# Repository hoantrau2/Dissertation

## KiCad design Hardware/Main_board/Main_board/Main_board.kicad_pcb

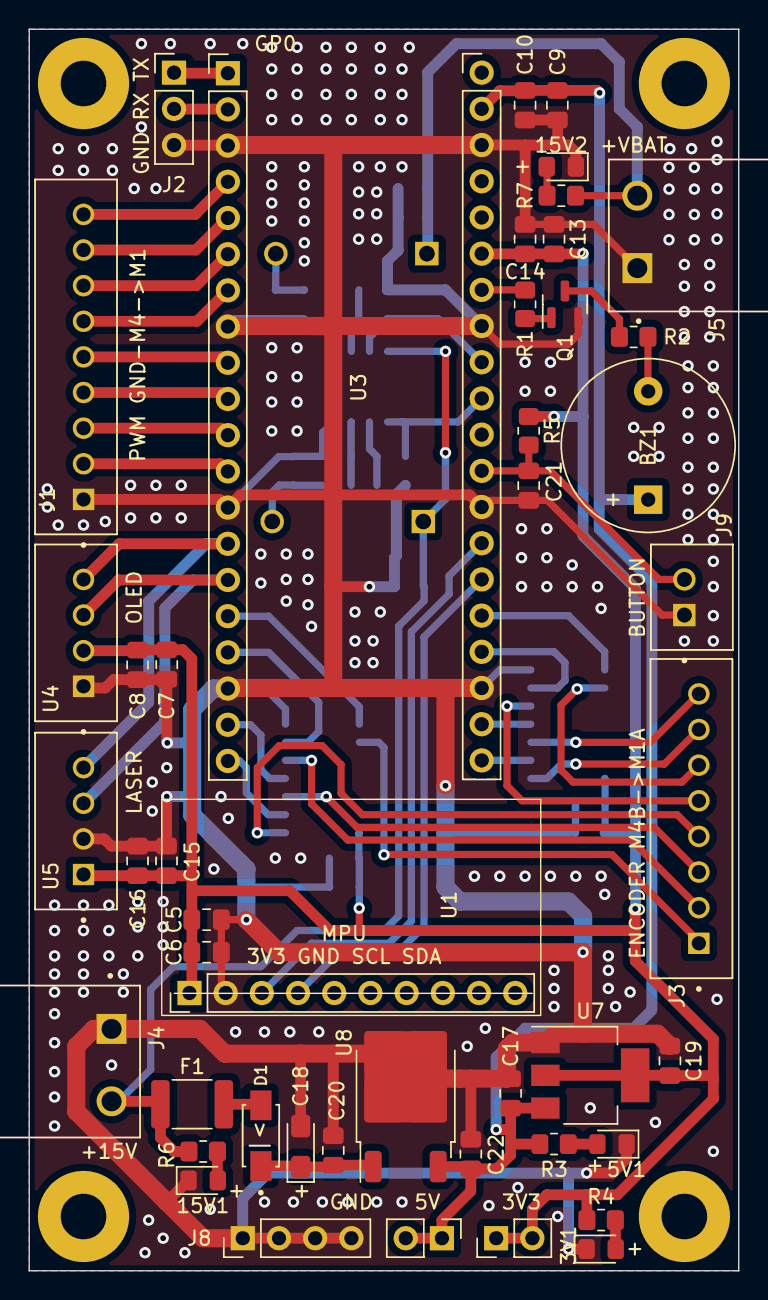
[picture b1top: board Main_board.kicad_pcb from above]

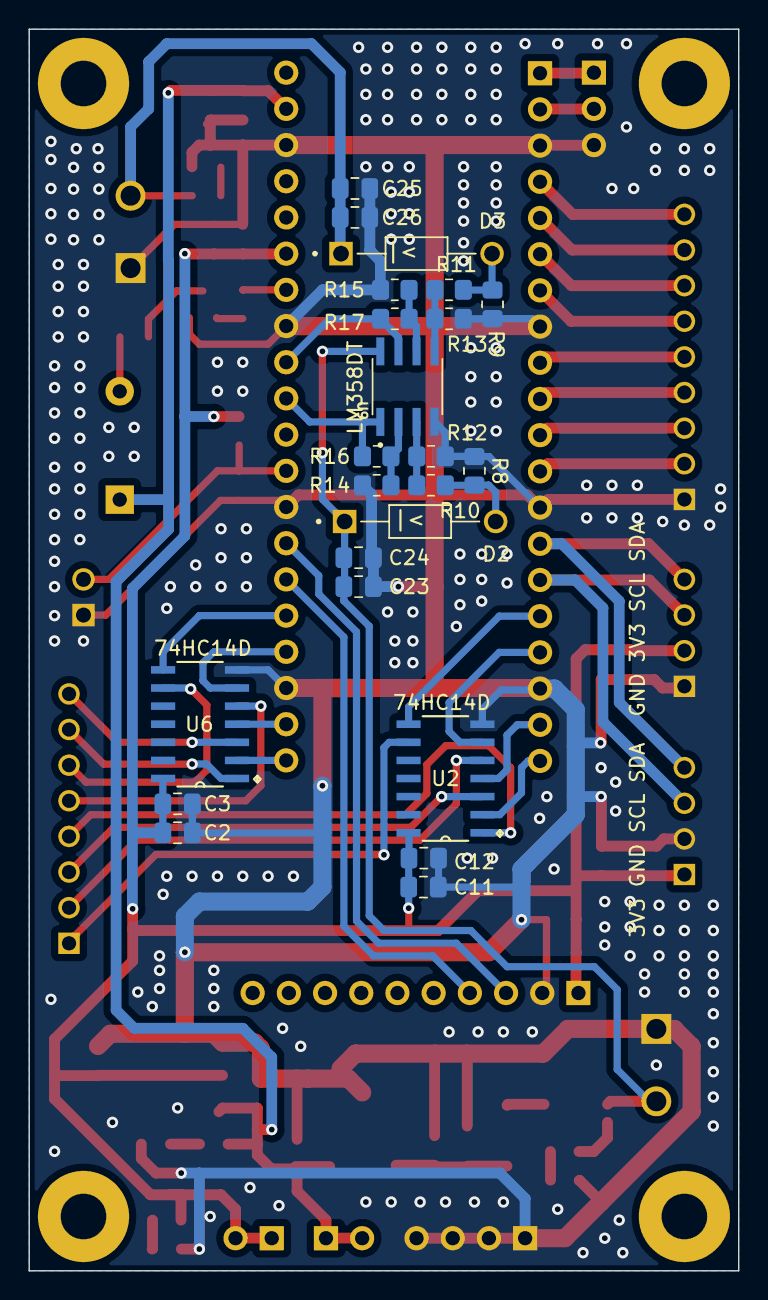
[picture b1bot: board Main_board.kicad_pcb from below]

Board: 2 copper layers, 49.8 x 87.1 mm, 73 parts (23 on the bottom side), 54 nets.

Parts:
3V1, 5V1, 15V1, 15V2: LED; LED_0805_2012Metric_Pad1.15x1.40mm_HandSolder
BZ1: Buzzer; Buzzer_12x9.5RM7.6
C2, C5, C7, C9, C11, C13, C15, C23, C25: 1u; C_0805_2012Metric_Pad1.18x1.45mm_HandSolder
C3, C6, C8, C10, C12, C14, C16, C17, C19, C21, C24, C26: 100n; C_0805_2012Metric_Pad1.18x1.45mm_HandSolder
C18: 1u, 16V; CP_EIA-3216-18_Kemet-A_Pad1.58x1.35mm_HandSolder
C20, C22: 100nF,50V; C_0805_2012Metric_Pad1.18x1.45mm_HandSolder
D1: RS1M; DIOM4330X250N
D2, D3: 1N4742A; DIOAD1060W70L435D230
F1: Fuse; Fuse_1812_4532Metric_Pad1.30x3.40mm_HandSolder
H1, H2, H3, H4: MountingHole; MountingHole_3.2mm_M3_Pad
J1: B9B-XH-A(LF)(SN); JST_B9B-XH-A(LF)(SN)
J2: Conn_01x03_Pin; PinHeader_1x03_P2.54mm_Vertical
J3: B8B-XH-A(LF)(SN); JST_B8B-XH-A(LF)(SN)
J4, J5: 282814-2; TE_282814-2
J6: Power 5V; PinHeader_1x02_P2.54mm_Vertical
J7: Power 3v3; PinHeader_1x02_P2.54mm_Vertical
J8: GND; PinHeader_1x04_P2.54mm_Vertical
J9: Button 1; JST_B2B-XH-A(LF)(SN)
Q1: 2SC1815; SOT-23
R1: 1k2; R_0805_2012Metric_Pad1.20x1.40mm_HandSolder
R2: 0R; R_0805_2012Metric_Pad1.20x1.40mm_HandSolder
R3: 1k; R_0805_2012Metric_Pad1.20x1.40mm_HandSolder
R4: 330; R_0805_2012Metric_Pad1.20x1.40mm_HandSolder
R5, R6, R7, R12, R13, R16, R17: 10k; R_0805_2012Metric_Pad1.20x1.40mm_HandSolder
R8, R9: 100k; R_0805_2012Metric_Pad1.20x1.40mm_HandSolder
R10, R11, R14, R15: 20k; R_0805_2012Metric_Pad1.20x1.40mm_HandSolder
U1: MPU9250
U2, U6: 74HC14D; SOIC127P600X175-14N
U3: pico_pin
U4, U5: JST_B4B-XH-A(LF)(SN)
U7: AMS1117-3.3; SOT-223-3_TabPin2
U8: L7805; TO-252-2
U9: LM358DT; SOIC127P600X175-8N

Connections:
+3V3: C2.2, C3.2, C5.2, C6.2, C7.2, C8.2, C11.2, C12.2, C13.2, C14.2, C15.2, C16.2, C19.2, J7.1, J7.2, R4.1, R5.1, U1.1 (VCC), U2.14 (VCC), U3.35, U4.2 (VCC), U5.1 (VIN), U6.14 (VCC), U7.2 (VO)
+5V: BZ1.1 (-), C9.2, C10.2, C17.2, C22.2, J6.1, J6.2, R3.1, U3.39, U7.3 (VI), U8.3 (OUT)
+15V: C23.1, C24.2, D2.C, F1.1, J4.2, R6.1, U9.8 (VCC+)
/RX: J2.2, U3.2
/TX: J2.1, U3.1
ADC0: R16.1, U3.31, U9.1 (OUT1)
ADC1: R17.1, U3.32, U9.7 (OUT2)
BUZZER1: R1.2, U3.34
Button1: C21.2, J9.2, R5.2, U3.29
GND: 3V1.1 (K), 5V1.1 (K), 15V1.1 (K), 15V2.1 (K), C2.1, C3.1, C5.1, C6.1, C7.1, C8.1, C9.1, C10.1, C11.1, C12.1, C13.1, C14.1, C15.1, C16.1, C17.1, C18.2, C19.1, C20.1, C21.1, C22.1, C23.2, C24.1, C25.2, C26.1, J1.1, J2.3, J4.1, J5.1, J8.1, J8.2, J8.3, J8.4, J9.1, Q1.2 (E), R8.2, R9.2, R12.2, R13.2, R14.1, R15.1, U1.2 (GND), U2.7 (GND), U3.3, U3.8, U3.13, U3.18, U3.23, U3.28, U3.33, U3.38, U4.1 (GND), U5.2 (GND), U6.7 (GND), U7.1 (GND), U8.2 (GND), U9.4 (VCC-)
M1_ENC_A: J3.8, U6.3 (2A)
M1_ENC_A': U3.22, U6.4 (2Y)
M1_ENC_B: J3.7, U6.1 (1A)
M1_ENC_B': U3.21, U6.2 (1Y)
M1_PWM_L: J1.8, U3.5
M1_PWM_R: J1.9, U3.4
M2_ENC_A: J3.6, U6.9 (4A)
M2_ENC_A': U3.25, U6.8 (4Y)
M2_ENC_B: J3.5, U6.5 (3A)
M2_ENC_B': U3.24, U6.6 (3Y)
M2_PWM_L: J1.6, U3.7
M2_PWM_R: J1.7, U3.6
M3_ENC_A: J3.4, U2.1 (1A)
M3_ENC_A': U2.2 (1Y), U3.20
M3_ENC_B: J3.3, U2.3 (2A)
M3_ENC_B': U2.4 (2Y), U3.19
M3_PWM_L: J1.4, U3.10
M3_PWM_R: J1.5, U3.9
M4_ENC_A: J3.2, U2.5 (3A)
M4_ENC_A': U2.6 (3Y), U3.17
M4_ENC_B: J3.1, U2.9 (4A)
M4_ENC_B': U2.8 (4Y), U3.16
M4_PWM_L: J1.2, U3.12
M4_PWM_R: J1.3, U3.11
MPU_SCL: U1.3 (SCL), U3.27
MPU_SDA: U1.4 (SDA), U3.26
unnamed: 3V1.2 (A), R4.2
unnamed: 5V1.2 (A), R3.2
unnamed: 15V1.2 (A), R6.2
unnamed: 15V2.2 (A), R7.2
unnamed: BZ1.2 (+), R2.1
unnamed: D1.A, F1.2
unnamed: D2.A, R8.1, R10.1
unnamed: D3.A, R9.1, R11.1
unnamed: Q1.1 (B), R1.1
unnamed: Q1.3 (C), R2.2
unnamed: C18.1, C20.2, D1.C, U8.1 (IN)
unnamed: R10.2, R12.1, U9.3 (IN1+)
unnamed: R14.2, R16.2, U9.2 (IN1-)
unnamed: R11.2, R13.1, U9.5 (IN2+)
unnamed: R15.2, R17.2, U9.6 (IN2-)
OLED_LASER_SCL: U3.15, U4.3 (SCK), U5.3 (SCL)
OLED_LASER_SDA: U3.14, U4.4 (SDA), U5.4 (SDA)
V_bat: C25.1, C26.2, D3.C, J5.2, R7.1

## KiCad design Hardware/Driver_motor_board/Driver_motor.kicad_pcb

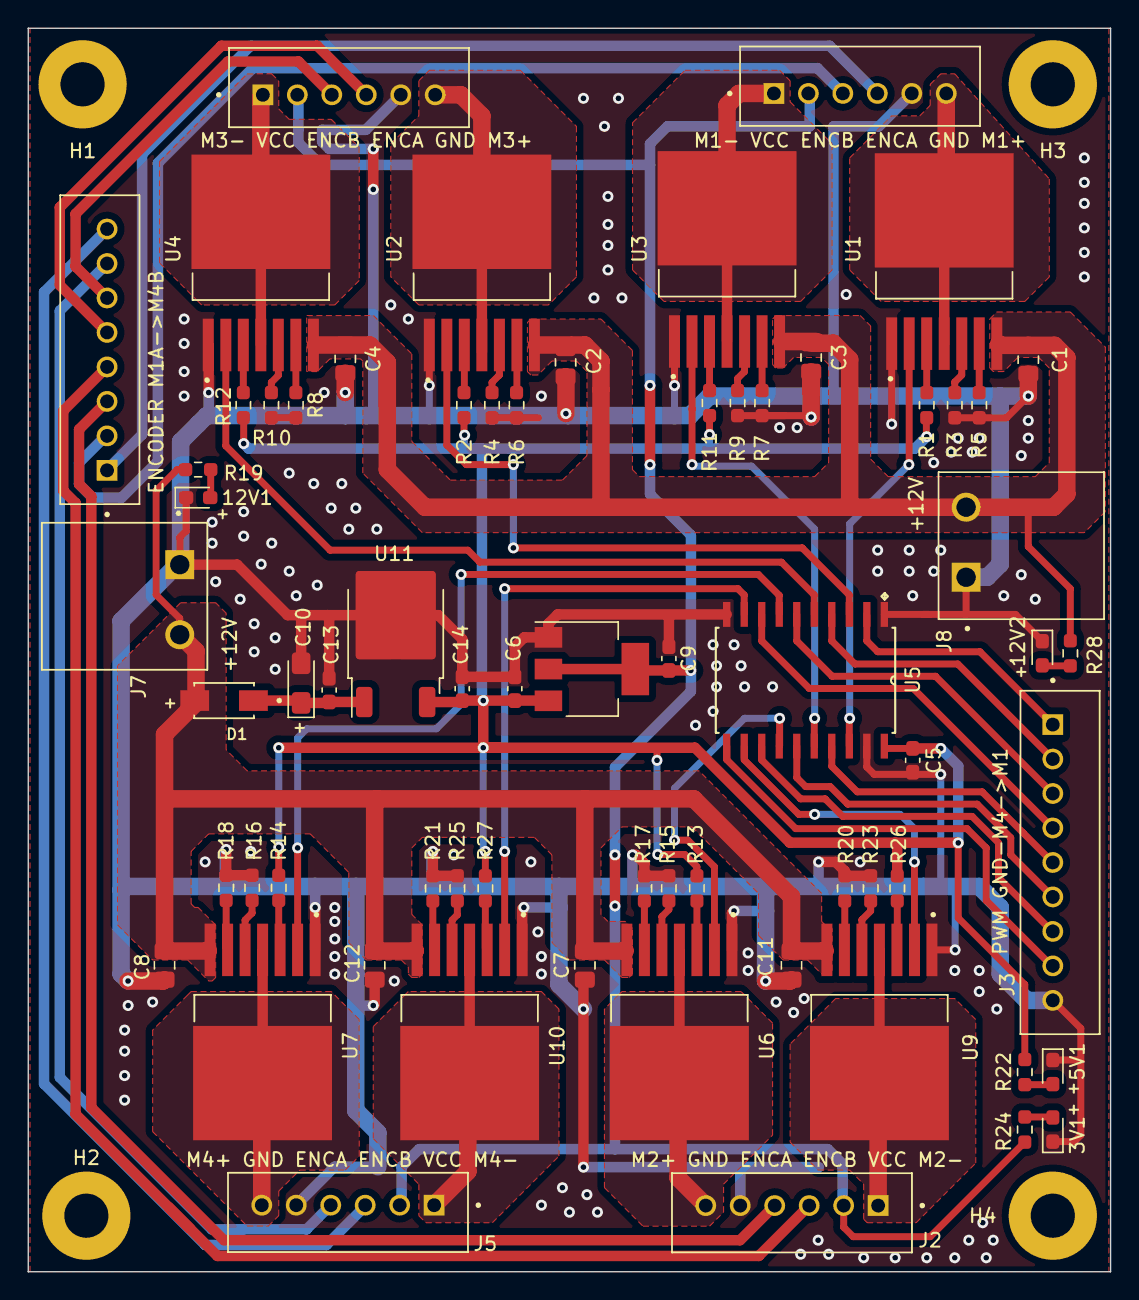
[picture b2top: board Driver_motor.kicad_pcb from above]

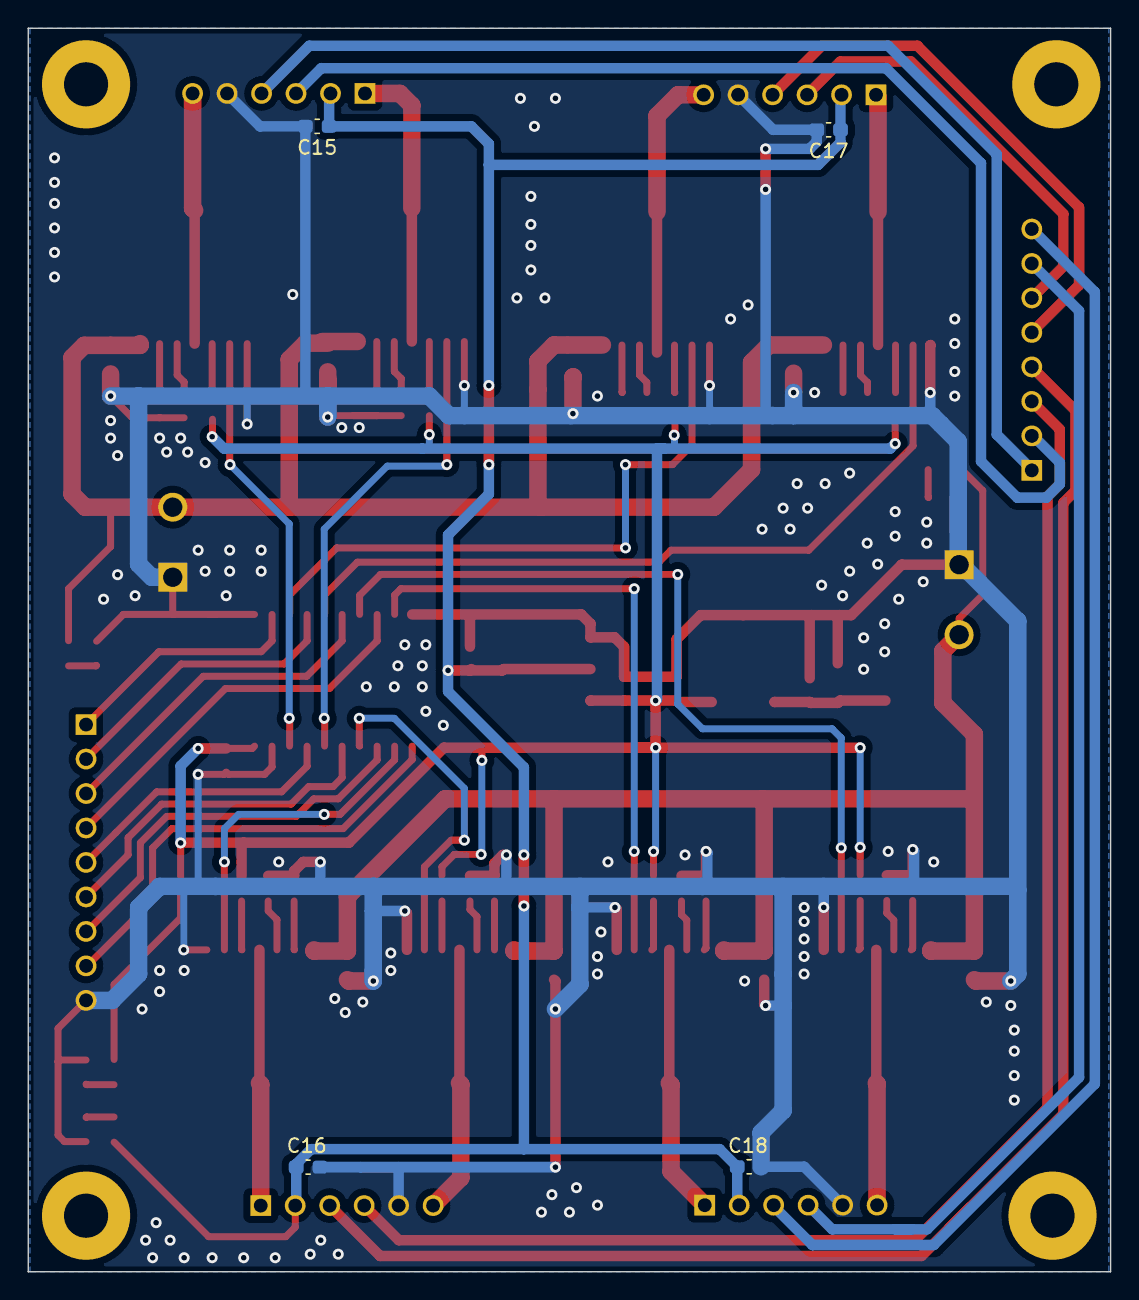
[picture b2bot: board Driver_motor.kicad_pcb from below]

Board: 2 copper layers, 78.5 x 90.2 mm, 74 parts (4 on the bottom side), 66 nets.

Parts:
3V1, 5V1, 12V1, 12V2: LED; LED_0603_1608Metric_Pad1.05x0.95mm_HandSolder
C1, C2, C3, C4, C7, C8, C11, C12: 470nF; C_0805_2012Metric_Pad1.18x1.45mm_HandSolder
C5: 100nF; C_0603_1608Metric_Pad1.08x0.95mm_HandSolder
C6, C9, C15, C16, C17, C18: 100n; C_0603_1608Metric_Pad1.08x0.95mm_HandSolder
C10: 1u, 16V; CP_EIA-3216-18_Kemet-A_Pad1.58x1.35mm_HandSolder
C13, C14: 100nF,50V; C_0603_1608Metric_Pad1.08x0.95mm_HandSolder
D1: RS1M; DIOM4330X250N
H1, H2, H3, H4: MountingHole; MountingHole_3.2mm_M3_Pad
J1, J2, J4, J5: B6B-XH-A(LF)(SN); JST_B6B-XH-A(LF)(SN)
J3: B9B-XH-A(LF)(SN); JST_B9B-XH-A(LF)(SN)
J6: B8B-XH-A(LF)(SN); JST_B8B-XH-A(LF)(SN)
J7, J8: 282814-2; TE_282814-2
R1, R2, R3, R4, R9, R10, R11, R12, R13, R14, R15, R16, R19, R23, R25, R26, R27, R28: 10k; R_0603_1608Metric_Pad0.98x0.95mm_HandSolder
R5, R6, R7, R8, R17, R18, R20, R21, R22: 1k; R_0603_1608Metric_Pad0.98x0.95mm_HandSolder
R24: 330; R_0603_1608Metric_Pad0.98x0.95mm_HandSolder
U1, U2, U3, U4, U6, U7, U9, U10: BTS7960B; DPAK127P1490X440-8N
U5: 74HC244; SOIC127P1032X265-20N
U8: AMS1117-3.3; SOT-223-3_TabPin2
U11: L7805; TO-252-2

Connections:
+3.3V: C9.2, C15.2, C16.2, C17.2, C18.2, J1.2, J2.2, J4.2, J5.2, R24.1, U8.2 (VO)
+5V: C5.1, C6.2, C14.2, R1.1, R2.1, R11.1, R12.1, R13.1, R14.1, R22.1, R26.1, R27.1, U5.20 (VCC), U8.3 (VI), U11.3 (OUT)
+12P: C1.2, C2.2, C3.1, C4.1, J8.2, R28.1, U1.7 (VS), U2.7 (VS), U3.7 (VS), U4.7 (VS)
+12V: C7.2, C8.2, C11.1, C12.1, D1.A, J7.2, R19.1, U6.7 (VS), U7.7 (VS), U9.7 (VS), U10.7 (VS)
GND: 3V1.1 (K), 5V1.1 (K), 12V1.1 (K), 12V2.1 (K), C1.1, C2.1, C3.2, C4.2, C5.2, C6.1, C7.1, C8.1, C9.1, C10.2, C11.2, C12.2, C13.1, C14.1, C15.1, C16.1, C17.1, C18.1, J1.5, J2.5, J3.9, J4.5, J5.5, J7.1, J8.1, R3.2, R4.2, R5.2, R6.2, R7.2, R8.2, R9.2, R10.2, R15.2, R16.2, R17.2, R18.2, R20.2, R21.2, R23.2, R25.2, U1.1 (GND), U2.1 (GND), U3.1 (GND), U4.1 (GND), U5.1 (1OE), U5.10 (GND), U5.19 (2OE), U6.1 (GND), U7.1 (GND), U8.1 (GND), U9.1 (GND), U10.1 (GND), U11.2 (GND)
M1+: J1.6, U1.4 (OUT), U1.8 (OUT)
M1-: J1.1, U3.4 (OUT), U3.8 (OUT)
M1_ENC_A: J1.4, J6.1
M1_ENC_B: J1.3, J6.2
M1_PWM_L: J3.2, U5.4 (1A1)
M1_PWM_L': U3.2 (IN), U5.16 (1Y1)
M1_PWM_R: J3.1, U5.2 (1A0)
M1_PWM_R': U1.2 (IN), U5.18 (1Y0)
M2+: J2.6, U6.4 (OUT), U6.8 (OUT)
M2-: J2.1, U9.4 (OUT), U9.8 (OUT)
M2_ENC_A: J2.4, J6.3
M2_ENC_B: J2.3, J6.4
M2_PWM_L: J3.4, U5.8 (1A3)
M2_PWM_L': U5.12 (1Y3), U9.2 (IN)
M2_PWM_R: J3.3, U5.6 (1A2)
M2_PWM_R': U5.14 (1Y2), U6.2 (IN)
M3+: J4.6, U2.4 (OUT), U2.8 (OUT)
M3-: J4.1, U4.4 (OUT), U4.8 (OUT)
M3_ENC_A: J4.4, J6.5
M3_ENC_B: J4.3, J6.6
M3_PWM_L: J3.6, U5.15 (2A1)
M3_PWM_L': U4.2 (IN), U5.5 (2Y1)
M3_PWM_R: J3.5, U5.17 (2A0)
M3_PWM_R': U2.2 (IN), U5.3 (2Y0)
M4+: J5.6, U7.4 (OUT), U7.8 (OUT)
M4-: J5.1, U10.4 (OUT), U10.8 (OUT)
M4_ENC_A: J5.4, J6.7
M4_ENC_B: J5.3, J6.8
M4_PWM_L: J3.8, U5.11 (2A3)
M4_PWM_L': U5.9 (2Y3), U10.2 (IN)
M4_PWM_R: J3.7, U5.13 (2A2)
M4_PWM_R': U5.7 (2Y2), U7.2 (IN)
unnamed: 3V1.2 (A), R24.2
unnamed: 5V1.2 (A), R22.2
unnamed: 12V1.2 (A), R19.2
unnamed: 12V2.2 (A), R28.2
unnamed: R1.2, U1.3 (INH)
unnamed: R5.1, U1.6 (IS)
unnamed: R3.1, U1.5 (SR)
unnamed: R2.2, U2.3 (INH)
unnamed: R6.1, U2.6 (IS)
unnamed: R4.1, U2.5 (SR)
unnamed: R11.2, U3.3 (INH)
unnamed: R7.1, U3.6 (IS)
unnamed: R9.1, U3.5 (SR)
unnamed: R12.2, U4.3 (INH)
unnamed: R8.1, U4.6 (IS)
unnamed: R10.1, U4.5 (SR)
unnamed: R13.2, U6.3 (INH)
unnamed: R17.1, U6.6 (IS)
unnamed: R15.1, U6.5 (SR)
unnamed: R14.2, U7.3 (INH)
unnamed: R18.1, U7.6 (IS)
unnamed: R16.1, U7.5 (SR)
unnamed: R26.2, U9.3 (INH)
unnamed: R20.1, U9.6 (IS)
unnamed: R23.1, U9.5 (SR)
unnamed: R27.2, U10.3 (INH)
unnamed: R21.1, U10.6 (IS)
unnamed: R25.1, U10.5 (SR)
unnamed: C10.1, C13.2, D1.C, U11.1 (IN)

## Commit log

2023-09-24 start to do dissertation
2023-09-24 add ws
2023-09-24 have error
2023-09-27 add driver motor board
2023-09-27 Initial error
2023-09-28 28 Sep 2023
2023-09-29 cut ws into home directory
2023-09-29 29 Sep morning
2023-09-30 evening 30 Step 2023
2023-10-02 add main board
2023-10-03 add note mapping
2023-10-05 5 oct 2023
2023-10-09 add template
2023-10-11 video demo
2023-10-22 add explain ICP
2023-10-23 after test board
2023-10-26 lidar on hardware
2023-11-01 add camera.xacro
2023-11-03 camera
2023-11-06 add ros2_controller
2023-11-06 Solving the problem EVERY robot has (with ros2_control)
2023-11-11 ROS2 on multiple machine and Diagonalizable matrix
2023-11-12 add scheduler
2023-11-14 app scheduler
2023-11-14 app adc
2023-11-15 Uros.docx
2023-11-28 edit some infor about ros2_control
2023-12-02 add joystick.launch.py
2023-12-04 add uros foxy
2023-12-10 add micro_ros
2023-12-24 resize mice 2nd Floor
2023-12-30 version
2023-12-30 add report
2023-12-31 add leture 3 in report
2023-12-31 add leture 4+5 in report
2024-01-01 add urdf file from soldwork
2024-01-01 add pico
2024-01-01 test uROS
2024-01-01 fix uROS seq1
2024-01-02 test git sep1
2024-01-02 add mapping picture
2024-01-02 test git seq2
2024-01-02 test git seq3
2024-01-02 test git seq4
2024-01-02 test git seq5
2024-01-02 test git seq6
2024-01-03 old file uros
2024-01-03 shortcut uROS
2024-01-06 final report
2024-03-11 add folder matlab
2024-03-17 pussh
2024-03-18 odom, base_link, base_footprint, lidar
2024-03-18 tf obtain the posion and veloity value
2024-03-21 read_lidar
2024-03-21 DE_algorithm
2024-03-22 inital
2024-03-23 add fuzzy_logic_controller
2024-03-26 bug bug bug
2024-03-29 bug bug
2024-03-29 initialized IMU node successfully
2024-03-29 rewrote read_IMU.cpp to be more compact and clear
2024-03-31 add fuzzy_node_test pid_node
2024-03-31 change initial parameters of pid node
2024-03-31 add fuzzy node and trajectories
2024-03-31 transfer duty and velocity
2024-03-31 pid node for testing
2024-03-31 fix encoder
2024-03-31 run successfully
2024-04-01 pico_node runs correctly
2024-04-01 checked fuzzy node
2024-04-03 stop motor
2024-04-03 add v,w actual
2024-04-03 back size data_vector 4
2024-04-03 in process tune pid
2024-04-05 tune pid parameters successfully
2024-04-05 add result PID tune
2024-04-05 start tuning fuzzy parameters
2024-04-05 convert Vleft Vright to omega and linear velocity
2024-04-06 fuzzy longitudinal controller and tune fuzzy node
2024-04-06 start fuzzy tuning
2024-04-06 fixed IMU successfully
2024-04-08 add stanley node
2024-04-10 change straight line and stanley node
2024-04-10 check stanley with lidar's message
2024-04-13 before convert to PD Fuzzy
2024-04-13 tune fuzzy succefully
2024-04-14 add result Fuzzy PD tune
2024-04-15 start writting controller
2024-04-17 writted thesis launch file
2024-04-17 first test
2024-04-17 error
2024-04-19 errorrrr
2024-04-19 add reference trajectory
2024-04-20 straight line successful
2024-04-21 add result line
2024-04-25 fix data_processing_node_straight
2024-04-27 tune successfully line
2024-04-28 started fixing zz
2024-04-29 circle
2024-04-30 before process data
2024-04-30 chose plot
2024-04-30 final data
2024-05-05 add result ref_eight
2024-07-15 push code for warm robot development
2024-07-15 re-push code for warm robot development
2024-07-15 push
2024-07-15 pushh
2024-07-15 committ
2024-07-15 re push code
2024-07-15 remove build, install, log folder in src
